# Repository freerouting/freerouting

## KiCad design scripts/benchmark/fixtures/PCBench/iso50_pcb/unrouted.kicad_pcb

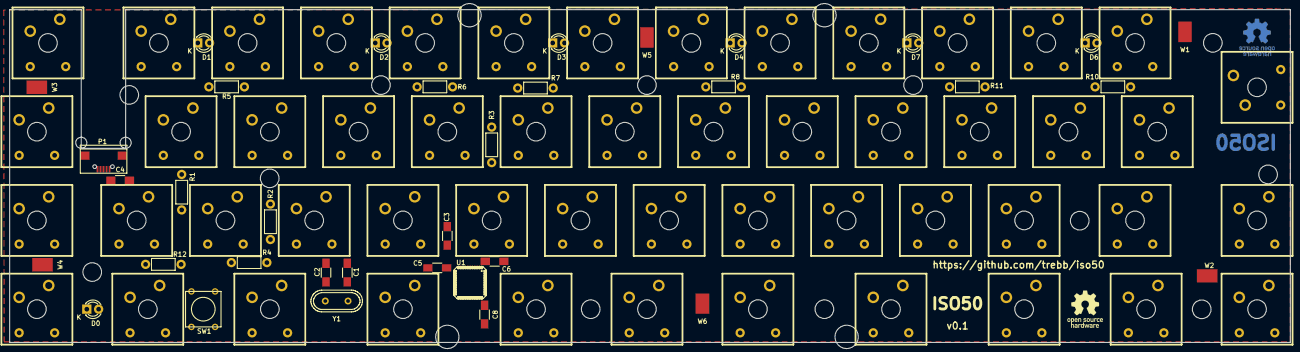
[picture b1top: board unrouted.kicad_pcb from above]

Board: 2 copper layers, 274.9 x 71.4 mm, 87 parts (0 on the bottom side), 95 nets, no tracks yet.

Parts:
C1, C2: 18p; C_1206_HandSoldering
C3, C4: 1u; C_1206_HandSoldering
C5, C6, C8: 100n; C_1206_HandSoldering
D0, D1, D2, D3, D4, D6, D7: Led_Small; LED-3MM
P1: USB; USB_Micro-207A-BBA0-R
R1, R2: 22; Resistor_Horizontal_RM7mm
R3, R4: 10k; Resistor_Horizontal_RM7mm
R5, R6, R7, R8, R10, R11, R12: 330; Resistor_Horizontal_RM7mm
SW1: SW_PUSH; SW_PUSH_SMALL
U00, U01, U02, U03, U04, U05, U06, U07, U08, U09, U10, U010, U11, U011, U12, U012, U13, U14, U15, U16, U17, U18, U19, U20, U21, U22, U23, U24, U25, U26, U27, U28, U29, U30, U31, U32, U34, U35, U37, U38, U110, U111, U112, U113, U210, U211, U212, U213, U310, U311, U312, U313: MX-DI; MXDIODE
U1: ATmega32U4; MLF-44_Atmel
W1, W2, W3, W4, W5, W6: TEST_1P; Spring-Contact_SMD
Y1: HC49S; Crystal_HC49-U_Vertical

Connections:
/col0: U00.4, U1.28, U10.4, U20.4, U30.4
/col1: U01.4, U1.27, U11.4, U21.4, U31.4
/col2: U1.26, U02.4, U12.4, U22.4, U32.4
/col3: U1.12, U03.4, U13.4, U23.4
/col4: U1.18, U04.4, U14.4, U24.4, U34.4
/col5: U1.8, U05.4, U15.4, U25.4, U35.4
/col6: U1.9, U06.4, U16.4, U26.4
/col7: U1.10, U07.4, U17.4, U27.4, U37.4
/col8: U1.40, U08.4, U18.4, U28.4, U38.4
/col9: U1.39, U09.4, U19.4, U29.4
/colA: U1.38, U010.4, U110.4, U210.4, U310.4
/colB: U1.37, U011.4, U111.4, U211.4, U311.4
/colC: U1.36, U012.4, U112.4, U212.4, U312.4
/colD: U1.30, U113.4, U213.4, U313.4
/led0: R12.2, U1.25
/led1: R5.2, U1.22
/led2: R6.2, U1.21
/led3: R7.2, U1.20
/led4: R8.2, U1.19
/led6: R10.2, U1.11
/led7: R11.2, U1.1
/row0: U00.2, U01.2, U1.31, U02.2, U03.2, U04.2, U05.2, U06.2, U07.2, U08.2, U09.2, U010.2, U011.2, U012.2
/row1: U1.32, U10.2, U11.2, U12.2, U13.2, U14.2, U15.2, U16.2, U17.2, U18.2, U19.2, U110.2, U111.2, U112.2, U113.2
/row2: U1.41, U20.2, U21.2, U22.2, U23.2, U24.2, U25.2, U26.2, U27.2, U28.2, U29.2, U210.2, U211.2, U212.2, U213.2
/row3: U1.29, U30.2, U31.2, U32.2, U34.2, U35.2, U37.2, U38.2, U310.2, U311.2, U312.2, U313.2
GND: C1.2, C2.2, C3.2, C4.2, C5.2, C6.2, C8.2, D0.1, D1.1, D2.1, D3.1, D4.1, D6.1, D7.1, P1.5, R3.2, SW1.2, W1.1, W2.1, W3.1, W4.1, W5.1, W6.1
unnamed: C1.1, U1.16, Y1.1
unnamed: C2.1, U1.17, Y1.2
unnamed: C3.1, U1.6
unnamed: D0.2, R12.1
unnamed: D1.2, R5.1
unnamed: D2.2, R6.1
unnamed: D3.2, R7.1
unnamed: D4.2, R8.1
unnamed: D6.2, R10.1
unnamed: D7.2, R11.1
unnamed: P1.2, R2.1
unnamed: P1.3, R1.1
unnamed: R1.2, U1.4
unnamed: R2.2, U1.3
unnamed: R3.1, U1.33
unnamed: R4.2, SW1.1, U1.13
unnamed: U00.1, U00.3
unnamed: U01.1, U01.3
unnamed: U02.1, U02.3
unnamed: U03.1, U03.3
unnamed: U04.1, U04.3
unnamed: U05.1, U05.3
unnamed: U06.1, U06.3
unnamed: U07.1, U07.3
unnamed: U08.1, U08.3
unnamed: U09.1, U09.3
unnamed: U10.1, U10.3
unnamed: U010.1, U010.3
unnamed: U11.1, U11.3
unnamed: U011.1, U011.3
unnamed: U12.1, U12.3
unnamed: U012.1, U012.3
unnamed: U13.1, U13.3
unnamed: U14.1, U14.3
unnamed: U15.1, U15.3
unnamed: U16.1, U16.3
unnamed: U17.1, U17.3
unnamed: U18.1, U18.3
unnamed: U19.1, U19.3
unnamed: U20.1, U20.3
unnamed: U21.1, U21.3
unnamed: U22.1, U22.3
unnamed: U23.1, U23.3
unnamed: U24.1, U24.3
unnamed: U25.1, U25.3
unnamed: U26.1, U26.3
unnamed: U27.1, U27.3
unnamed: U28.1, U28.3
unnamed: U29.1, U29.3
unnamed: U30.1, U30.3
unnamed: U31.1, U31.3
unnamed: U32.1, U32.3
unnamed: U34.1, U34.3
unnamed: U35.1, U35.3
unnamed: U37.1, U37.3
unnamed: U38.1, U38.3
unnamed: U110.1, U110.3
unnamed: U111.1, U111.3
unnamed: U112.1, U112.3
unnamed: U113.1, U113.3
unnamed: U210.1, U210.3
unnamed: U211.1, U211.3
unnamed: U212.1, U212.3
unnamed: U213.1, U213.3
unnamed: U310.1, U310.3
unnamed: U311.1, U311.3
unnamed: U312.1, U312.3
unnamed: U313.1, U313.3
VCC: C4.1, C5.1, C6.1, C8.1, P1.1, R4.1, U1.2, U1.7, U1.14, U1.24, U1.34, U1.44

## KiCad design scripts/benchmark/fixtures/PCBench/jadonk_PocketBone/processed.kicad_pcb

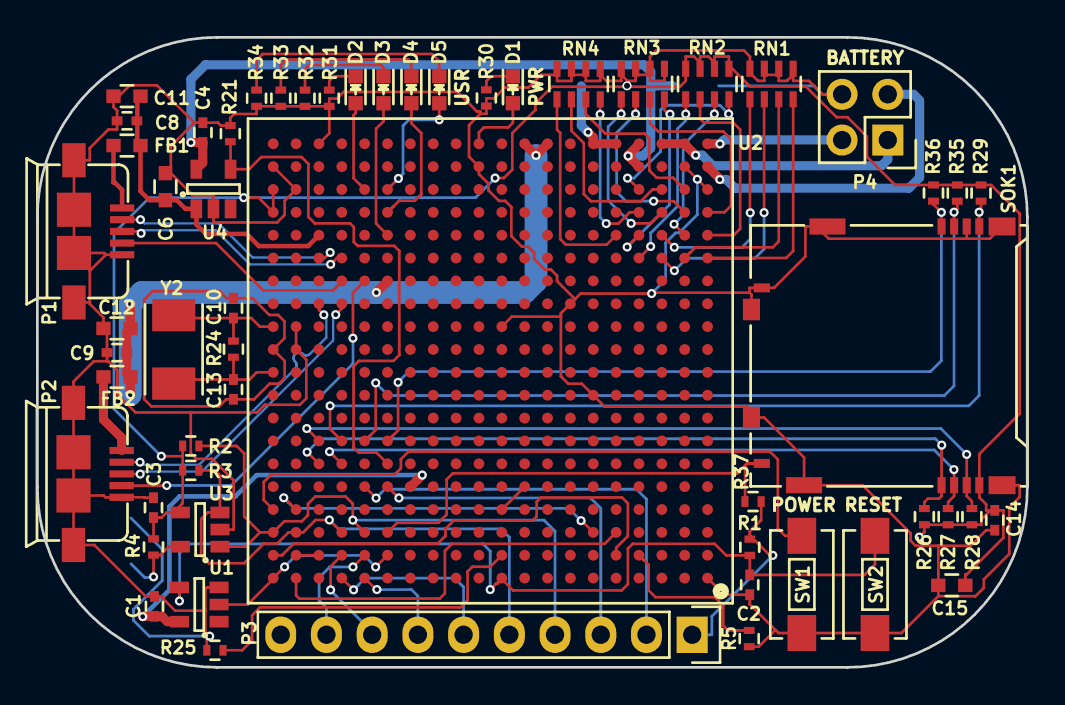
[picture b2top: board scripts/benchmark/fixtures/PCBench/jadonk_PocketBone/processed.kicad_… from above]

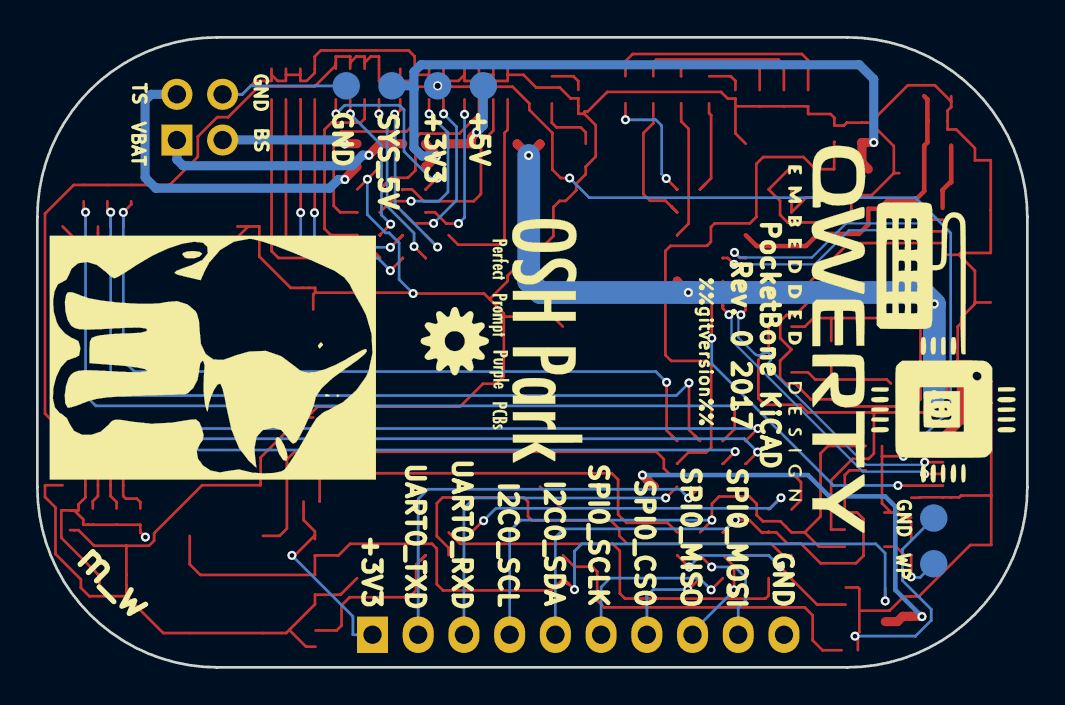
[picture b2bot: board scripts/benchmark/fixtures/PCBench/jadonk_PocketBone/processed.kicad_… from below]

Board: 4 copper layers, 55.0 x 35.0 mm, 62 parts (6 on the bottom side), 74 nets.

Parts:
C1, C3, C4, C8, C9, C14: 0.1uF; C_0402
C2: 1uF; C_0402
C6, C11, C12, C15: 10uF; C_0603
C10, C13: 18pF; C_0402
D1, D2, D3, D4, D5: BLUE; LED-0603
FB1, FB2: FILTER; C_0603
P1, P2: USB_OTG; USB_MICRO_B_ST-USB-001E
P3: CONN_01X10; Socket_Strip_Straight_1x10
P4: CONN_02X02; Socket_Strip_Straight_2x02
R1, R5, R26, R27, R28, R29, R35, R36, R37: 10K; R_0402
R2, R3, R4: 1.5K; R_0402
R21: 100K; R_0402
R24: 1M; R_0402
R25: 4.87K; R_0402
R30: 4.7K; R_0402
R31, R32, R33, R34: 240; R_0402
RN1, RN2, RN3, RN4: 100K; R_Array_Concave_4x0603
SOK1: SCHA5B0200
SW1, SW2: SW_PUSH_SMALL_H; SW_SPST_EVQPE1
TP1: 5V; Measurement_Point_Round-SMD-Pad_Small
TP2: WP; Measurement_Point_Round-SMD-Pad_Small
TP3, TP6: GND; Measurement_Point_Round-SMD-Pad_Small
TP4: 3P3; Measurement_Point_Round-SMD-Pad_Small
TP5: SYS_5V; Measurement_Point_Round-SMD-Pad_Small
U1: SN74LVC1G07; SOT-23-5
U2: OSD3358; BGA-400-1-27mm
U3: 24LC32AT-I/OT; SOT-23-5
U4: TPS2051C; SOT-23-5
Y2: 24MHz; 445C33D24M00000

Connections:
3P3AUX: D1.2, U2.Y11
+3V3: C3.1, C14.1, C15.1, P3.1, R1.1, R2.1, R3.1, R4.1, R26.1, R27.1, R28.1, R29.1, R35.1, R36.1, R37.1, RN2.5, RN2.6, RN2.7, RN2.8, SOK1.4, TP4.1, U2.U20, U2.V20, U3.4
+5V: TP1.1, U2.Y5, U2.Y6
BAT_SENSE: P4.3, U2.Y1
GND: C1.2, C2.2, C3.2, C4.2, C6.2, C8.2, C9.2, C11.2, C12.2, C14.2, C15.2, P1.5, P1.6, P1.7, P1.8, P1.9, P2.5, P2.6, P2.7, P2.8, P2.9, P3.10, P4.4, R5.2, R21.2, R25.1, R30.1, R31.1, R32.1, R33.1, R34.1, RN1.1, RN1.2, RN1.3, RN1.4, RN3.1, RN3.2, RN3.3, RN3.4, RN4.1, RN4.2, RN4.3, RN4.4, SOK1.6, SOK1.10, SOK1.11, SW1.1, SW2.1, TP3.1, TP6.1, U1.3, U2.A1, U2.J6, U2.L19, U2.M10, U2.M19, U2.N7, U2.V1, U2.V19, U2.W2, U2.W11, U2.W20, U2.Y18, U3.2, U4.2
I2C0_SCL: P3.4, R2.2, U2.C16, U2.C20, U3.1
I2C0_SDA: P3.5, R3.2, U2.C17, U2.C19, U3.3
MMC0_CD: R37.2, SOK1.9, U2.C15
MMC0_CLK: R29.2, SOK1.5, U2.G17
MMC0_CMD: R28.2, SOK1.3, U2.G18
MMC0_DAT0: R35.2, SOK1.7, U2.G16
MMC0_DAT1: R36.2, SOK1.8, U2.G15
MMC0_DAT2: R26.2, SOK1.1, U2.F18
MMC0_DAT3: R27.2, SOK1.2, U2.F17
unnamed: C2.1, R1.2, SW2.2, U1.4, U2.A10
unnamed: C10.1, R24.2, U2.M20, Y2.1
unnamed: C13.1, R24.1, U2.K20, Y2.2
unnamed: D1.1, R30.2
unnamed: D2.1, R31.2
unnamed: D3.1, R32.2
unnamed: D4.1, R33.2
unnamed: D5.1, R34.2
unnamed: FB1.2, P1.1
unnamed: FB2.2, P2.1
unnamed: R4.2, TP2.1, U3.5
unnamed: R5.1, U2.B4
unnamed: RN1.5, U2.T3
unnamed: RN1.6, U2.R3
unnamed: RN1.7, U2.R2
unnamed: RN1.8, U2.R1
unnamed: RN2.1, U2.R4
unnamed: RN2.2, U2.T1
unnamed: RN2.3, U2.T2
unnamed: RN2.4, U2.V4
unnamed: RN3.5, U2.U3
unnamed: RN3.6, U2.U2
unnamed: RN3.7, U2.U1
unnamed: RN3.8, U2.T4
unnamed: RN4.5, U2.T5
unnamed: RN4.6, U2.V3
unnamed: RN4.7, U2.V2
unnamed: RN4.8, U2.U4
unnamed: SW1.2, U2.D20
unnamed: U2.A19, U2.C5
unnamed: U2.B18, U2.B19
unnamed: U2.B5, U2.B20
unnamed: U2.C6, U2.D19
OSC0_GND: C10.2, C13.2, U2.L20
PMIC_PGOOD: U1.2, U2.A20, U2.B15
SPI_CLK: P3.6, U2.A17
SPI_CS0: P3.7, U2.A16
SPI_MISO: P3.8, U2.B17
SPI_MOSI: P3.9, U2.B16
SYS_5V: C4.1, TP5.1, U2.W4, U2.Y4, U4.5
TRSTN: R25.2, U2.B10
TS: P4.2, U2.W1
UART0_RXD: P3.3, U2.E15
UART0_TXD: P3.2, U2.E16
USB0_D_N: P2.2, U2.N18
USB0_D_P: P2.3, U2.N17
USB0_ID: P2.4, U2.P16
USB0_VBUS: C9.1, C12.1, FB2.1, U2.P15, U2.Y8, U2.Y9
USB1_DRVVBUS: R21.1, U2.F15, U4.4
USB1_D_N: P1.2, U2.R18
USB1_D_P: P1.3, U2.R17
USB1_ID: P1.4, U2.P17
USB1_VBUS: C6.1, C8.1, C11.1, FB1.1, U2.T18, U4.1
USR0_LED: D5.2, U2.V15
USR1_LED: D4.2, U2.U15
USR2_LED: D3.2, U2.T15
USR3_LED: D2.2, U2.V16
VBAT: P4.1, U2.Y2, U2.Y3
VDD_1V8: U2.D10, U2.E9
VDD_RTC: C1.1, U1.5, U2.E14

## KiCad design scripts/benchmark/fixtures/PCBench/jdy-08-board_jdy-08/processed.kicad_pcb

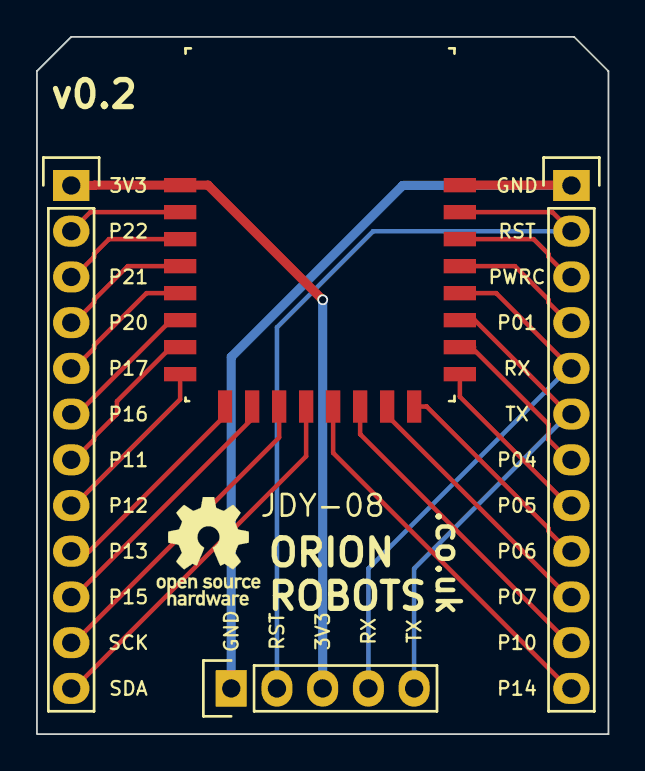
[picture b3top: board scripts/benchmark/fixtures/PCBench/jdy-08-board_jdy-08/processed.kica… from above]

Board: 2 copper layers, 31.8 x 38.7 mm, 4 parts (0 on the bottom side), 24 nets.

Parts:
P1: CONN_01X05; Socket_Strip_Straight_1x05
P2, P3: CONN_01X12; Socket_Strip_Straight_1x12
U1: JDY-08

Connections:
+3V3: P1.3, P2.1, U1.1
/P00: P3.3, U1.22
/P01: P3.4, U1.21
/P04: P3.7, U1.18
/P05: P3.8, U1.17
/P06: P3.9, U1.16
/P07: P3.10, U1.15
/P10: P3.11, U1.14
/P11: P2.7, U1.7
/P12: P2.8, U1.8
/P13: P2.9, U1.9
/P14: P3.12, U1.13
/P15: P2.10, U1.10
/P16: P2.6, U1.6
/P17: P2.5, U1.5
/P20: P2.4, U1.4
/P21: P2.3, U1.3
/P22: P2.2, U1.2
/RST: P1.2, P3.2, U1.23
/RX: P1.4, P3.5, U1.20
/SCK: P2.11, U1.11
/SDA: P2.12, U1.12
/TX: P1.5, P3.6, U1.19
GND: P1.1, P3.1, U1.24

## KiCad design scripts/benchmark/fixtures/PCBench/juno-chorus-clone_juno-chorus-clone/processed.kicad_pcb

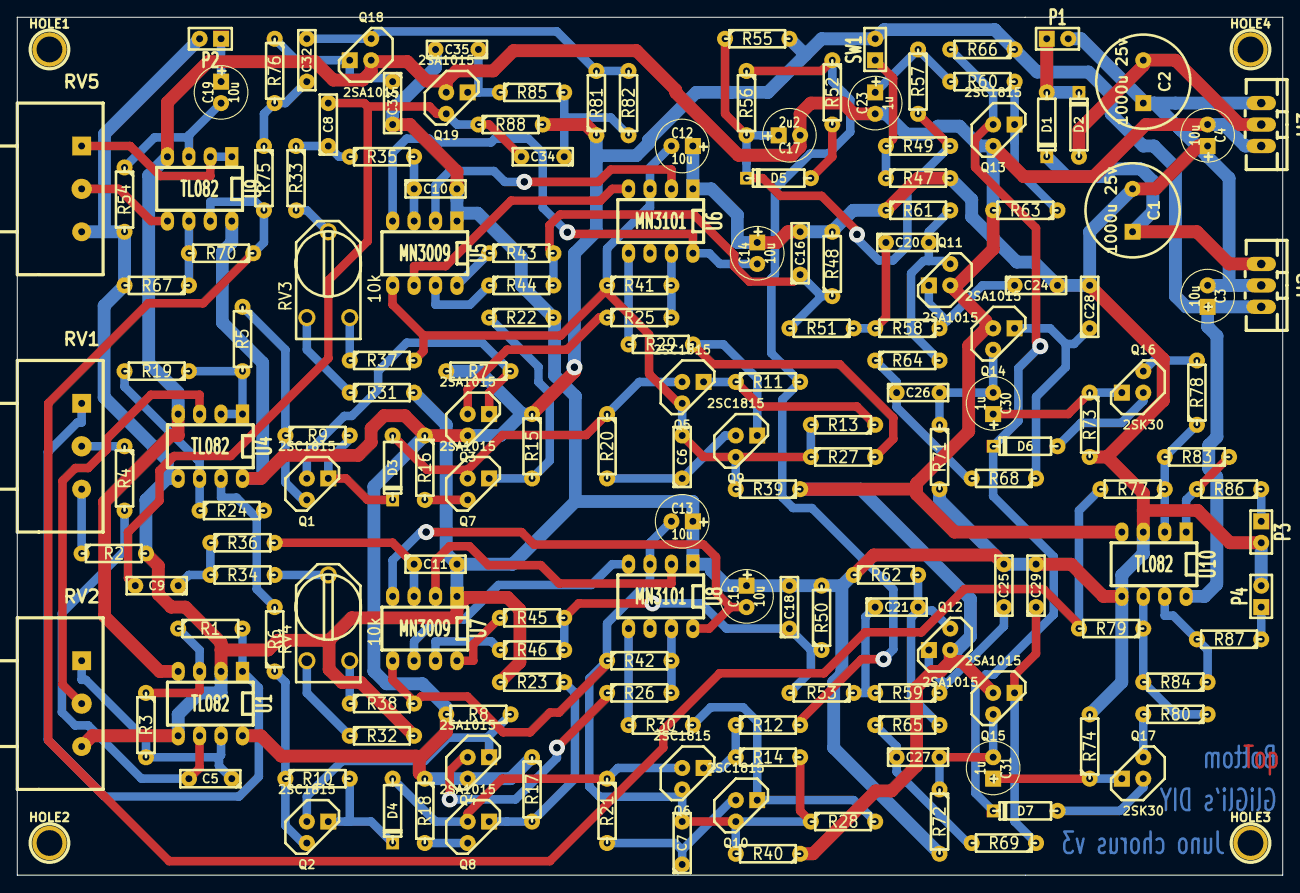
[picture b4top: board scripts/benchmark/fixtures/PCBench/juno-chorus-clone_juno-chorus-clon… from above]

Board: 2 copper layers, 149.9 x 101.6 mm, 172 parts (0 on the bottom side), 107 nets.

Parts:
C1, C2: 1000u 25v; C2V10
C3, C4, C12, C13, C14, C15, C19: 10u; C1V7
C5, C8, C9: 100n; C2
C6, C7: 150p; C2
C10, C11, C16, C18: 2n2; C2
C17: 2u2; C1V7
C20, C21, C32: 820p; C2
C23, C30, C31: 1u; C1V7
C24, C25, C33: 680p; C2
C26, C27, C34: 1n8; C2
C28, C29, C35: 270p; C2
D1, D2: 1N5817; D3
D3, D4, D5, D6, D7: 1N4148; D3
HOLE1, HOLE2, HOLE3, HOLE4: P***; 1pin
P1: 15VAC_IN; SIL-2
P2: AUDIO_IN; SIL-2
P3: AUDIO_OUT_1; SIL-2
P4: AUDIO_OUT_2; SIL-2
Q1, Q2, Q5, Q6, Q9, Q10, Q13: 2SC1815; TO92-123
Q3, Q4, Q7, Q8, Q11, Q12, Q14, Q15, Q18, Q19: 2SA1015; TO92-123
Q16, Q17: 2SK30; TO92DGS
R1, R48, R50, R77, R79: 47k; R3-LARGE_PADS
R2, R22, R23, R35, R36, R52, R55, R66, R67, R71, R72, R83, R84, R88: 10k; R3-LARGE_PADS
R3, R9, R10, R13, R14, R54, R70: 33k; R3-LARGE_PADS
R4: 1M; R3-LARGE_PADS
R5, R6, R47, R86, R87: 1k; R3-LARGE_PADS
R7, R8, R25, R26, R27, R28: 2k2; R3-LARGE_PADS
R11, R12, R56: 330k; R3-LARGE_PADS
R15, R17, R41, R42: 1k8; R3-LARGE_PADS
R16, R18: 8k2; R3-LARGE_PADS
R19, R24: 470k; R3-LARGE_PADS
R20, R21: 6k8; R3-LARGE_PADS
R29, R30, R51, R53, R58, R59, R61, R62, R64, R65, R68, R69, R73, R74, R75, R76, R81, R82, R85: 22k; R3-LARGE_PADS
R31, R32: 15k; R3-LARGE_PADS
R33, R34: 100k; R3-LARGE_PADS
R37, R38: 12k; R3-LARGE_PADS
R39, R40: 10; R3-LARGE_PADS
R43, R44, R45, R46: 3k3; R3-LARGE_PADS
R49: 330; R3-LARGE_PADS
R57: 150k; R3-LARGE_PADS
R60: 560k; R3-LARGE_PADS
R63, R78, R80: 39k; R3-LARGE_PADS
RV1, RV2, RV5: 100k; POTA_Fav
RV3, RV4: 10k; RV2X4
SW1: SW_PUSH; SIL-2
U1, U4, U9, U10: TL082; DIP-8__300_ELL
U2: LM7815CT; TO-220_Neutral123_Vertical_LargePads
U3: LM7915CT; TO-220_Neutral123_Vertical_LargePads
U5, U7: MN3009; DIP-8__300_ELL
U6, U8: MN3101; DIP-8__300_ELL

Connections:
-VAA: C4.2, C17.2, C23.2, Q11.2, Q12.2, Q13.1, Q14.2, Q15.2, Q18.2, Q19.2, R39.1, R40.1, R63.2, U1.4, U3.3, U4.4, U9.4, U10.4
GND: C1.2, C2.1, C3.2, C4.1, C10.2, C11.2, C12.1, C13.1, C14.1, C15.1, C16.2, C18.2, C24.2, C25.2, C28.2, C29.2, C33.2, C35.2, P1.2, P2.2, P3.2, P4.2, R2.2, R22.2, R23.2, R31.2, R32.2, R47.2, R48.2, R50.2, R54.2, R61.1, R62.1, R67.2, R71.2, R72.2, R73.2, R74.2, RV2.3, RV5.3, U1.2, U1.5, U2.2, U3.1, U4.5, U5.1, U6.1, U7.1, U8.1, U10.3, U10.5
unnamed: U5.2, U6.2
unnamed: R37.1, RV3.3
unnamed: R25.2, R41.2, U6.7
unnamed: C6.1, Q9.2, R20.2
unnamed: Q5.3, R11.1, R13.1
unnamed: R31.1, RV3.1
unnamed: R29.1, U6.5
unnamed: Q7.3, R15.2, R22.1
unnamed: Q9.3, R27.2, R29.2
unnamed: Q7.1, R16.2
unnamed: C6.2, C12.2, Q5.1, Q9.1, R13.2, R27.1, R37.2, R39.2, R41.1, U5.5, U6.3
unnamed: D3.2, Q1.3, R9.2
unnamed: Q3.2, R25.1
unnamed: D3.1, Q5.2, Q7.2, R20.1
unnamed: Q1.2, Q3.3, R7.1
unnamed: C27.1, R65.1, R69.2
unnamed: C29.1, Q15.3, R69.1
unnamed: C27.2, C31.2, Q15.1, R72.1
unnamed: C21.2, Q12.1, R62.2, R65.2
unnamed: C21.1, R53.1, R59.2
unnamed: C31.1, Q17.D, R74.1
unnamed: R84.1, R87.2, U10.7
unnamed: C25.1, Q12.3, R59.1
unnamed: Q1.1, R5.1, R9.1
unnamed: R79.1, R80.1, R84.2, U10.6
unnamed: P4.1, R87.1
unnamed: C14.2, U5.4, U6.8
unnamed: P3.1, R86.1
unnamed: C33.1, Q18.3, R76.1
unnamed: C20.1, R51.1, R58.2
unnamed: R83.1, R86.2, U10.1
unnamed: R77.1, R78.1, R83.2, U10.2
unnamed: C19.1, P2.1
unnamed: R70.1, R75.2, R77.2, R79.2, U9.7
unnamed: R67.1, R70.2, U9.6
unnamed: C32.1, R75.1, R76.2
unnamed: RV5.2, U9.5
unnamed: RV5.1, U9.1, U9.2
unnamed: C35.1, Q19.3, R85.1
unnamed: C34.1, R82.1, R85.2
unnamed: C20.2, Q11.1, R61.2, R64.2
unnamed: C32.2, Q18.1, R81.2, R82.2
unnamed: C16.1, R43.2, R44.2, R48.1, R51.2
unnamed: R33.2, RV3.2
unnamed: R43.1, U5.8
unnamed: R44.1, U5.7
unnamed: C10.1, R35.2, U5.3
unnamed: U5.6, U6.4
unnamed: C8.1, R33.1, R35.1
unnamed: C24.1, Q11.3, R58.1
unnamed: C26.1, R64.1, R68.2
unnamed: C28.1, Q14.3, R68.1
unnamed: C26.2, C30.2, Q14.1, R71.1
unnamed: C30.1, Q16.D, R73.1
unnamed: D6.1, Q16.G
unnamed: Q16.S, R78.2
unnamed: Q17.S, R80.2
unnamed: D5.1, R52.2
unnamed: R11.2, R12.2, R52.1, R56.1
unnamed: D6.2, D7.2, Q13.2, R66.2
unnamed: R47.1, R49.2, SW1.1
unnamed: C8.2, C9.2, C34.2, Q19.1, R88.1
unnamed: C23.1, R57.1, R60.2
unnamed: Q13.3, R60.1, R63.1
unnamed: C17.1, D5.2, R49.1, R55.1, R56.2, R57.2
unnamed: Q8.1, R18.2
unnamed: Q4.2, R26.1
unnamed: R6.2, R24.2, U4.7
unnamed: R19.2, R24.1, U4.6
unnamed: Q2.1, R6.1, R10.1
unnamed: U7.6, U8.4
unnamed: D4.1, Q6.2, Q8.2, R21.1
unnamed: Q2.2, Q4.3, R8.1
unnamed: C11.1, R36.2, U7.3
unnamed: R45.1, U7.8
unnamed: R46.1, U7.7
unnamed: R34.2, RV4.2
unnamed: C9.1, R34.1, R36.1
unnamed: D7.1, Q17.G
unnamed: U7.2, U8.2
unnamed: D4.2, Q2.3, R10.2
unnamed: C18.1, R45.2, R46.2, R50.1, R53.2
unnamed: Q10.3, R28.2, R30.2
unnamed: R26.2, R42.2, U8.7
unnamed: R32.1, RV4.1
unnamed: R30.1, U8.5
unnamed: Q8.3, R17.2, R23.1
unnamed: RV2.2, U4.3
unnamed: C15.2, U7.4, U8.8
unnamed: C7.1, Q10.2, R21.2
unnamed: Q6.3, R12.1, R14.1
unnamed: R38.1, RV4.3
unnamed: C7.2, C13.2, Q6.1, Q10.1, R14.2, R28.1, R38.2, R40.2, R42.1, U7.5, U8.3
unnamed: R2.1, RV1.3
unnamed: C5.1, R3.2, RV2.1, U1.7
unnamed: R4.1, RV1.2
unnamed: C2.2, D2.1, U3.2
unnamed: D1.1, D2.2, P1.1
unnamed: R1.2, RV1.1, U1.1
unnamed: C1.1, D1.2, U2.1
unnamed: R5.2, R19.1, U4.1, U4.2
unnamed: C19.2, R54.1, U9.3
unnamed: C5.2, R4.2, U1.6
unnamed: R1.1, R3.1, U1.3
VAA: C3.1, Q3.1, Q4.1, R7.2, R8.2, R15.1, R16.1, R17.1, R18.1, R55.2, R66.1, R81.1, R88.2, SW1.2, U1.8, U2.3, U4.8, U9.8, U10.8
